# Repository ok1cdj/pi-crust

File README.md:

Pi Crust
========

This is a PCB that brings sanity to Raspberry Pi headers.

See [http://picru.st](http://picru.st) for more.

Features
--------

*   Really compact - sits *inside* the surface area of the Raspberry Pi and adds less than 2mm to the height. If you have a case for your Raspberry Pi, this board should fit inside it.
*   Pins are grouped together: GPIO, I2C, SPI, UART and power.
*   Every pin is clearly labelled added labels for RPi revision 1 and 2.
*   Connections: 2 x SPI, 2 x I2C, 1 x UART, 8 x GPIO
*   Added bidirectional 2 ports level converter
*   Uses female headers instead of male headers - you can poke jumpers right in.
*   Lots of GND and 5V pins - you need those guys a lot. These pins are duplicated where it makes sense (e.g. within the UART, I2C and SPI groups).
*   All thru-hole components - you can solder it yourself.
*   Cheapety cheapy cheap.
*   Open source hardware.
*   [More photos here](http://todayimade.co/items/joe-walnes-made-a-tiny-breakout-board-for-raspberry-pi)

See [http://picru.st](http://picru.st) for more.

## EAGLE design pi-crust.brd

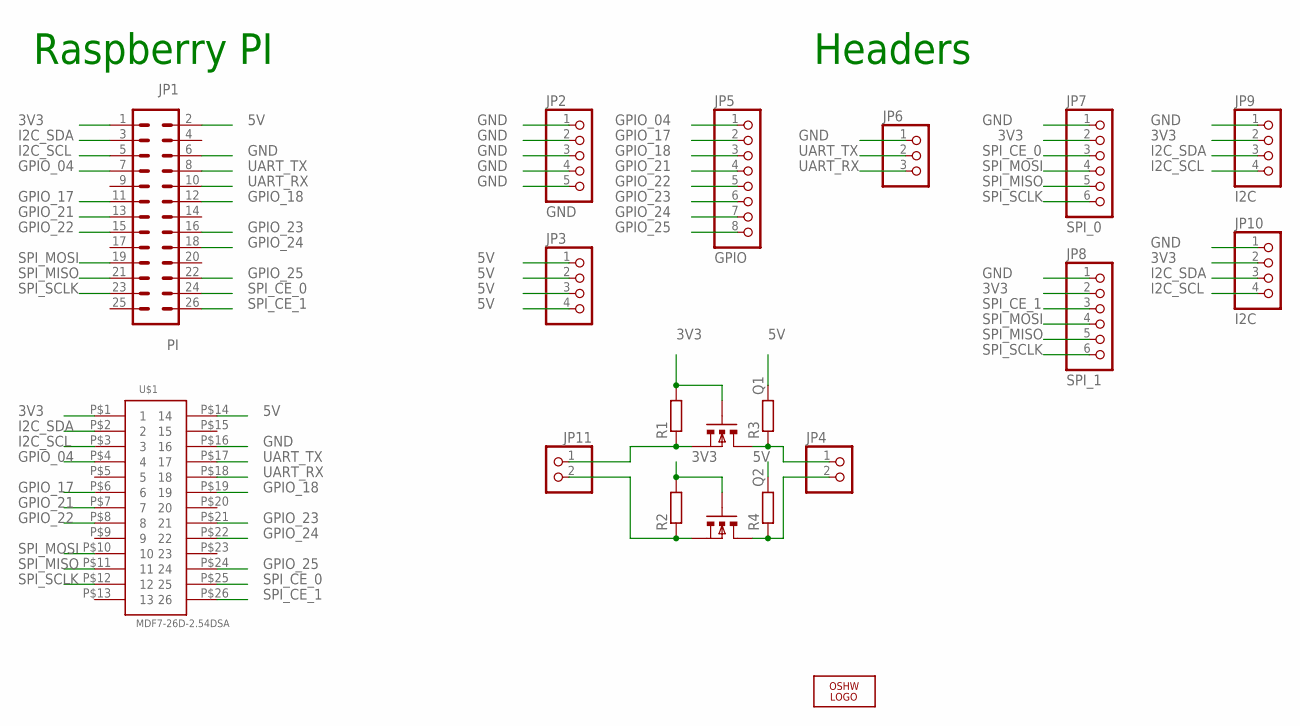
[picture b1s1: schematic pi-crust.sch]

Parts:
JP1: PI; MA13-2
JP2: GND; 1X05
JP3: PINHD-1X4; 1X04
JP4, JP11: PINHD-1X2; 1X02
JP5: GPIO; 1X08
JP6: PINHD-1X3; 1X03
JP7: SPI_0; 1X06
JP8: SPI_1; 1X06
JP9, JP10: I2C; 1X04
LOGO1: OSHW_LOGO_8MILX0100-NT; OSHW_8X100_NOTEXT
Q1, Q2: BSS138SMD; SOT23
R1, R2, R3, R4: R-EU_R0603; R0603
U$1: MDF7-26D-2.54DSA

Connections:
3V3: JP1.1, JP7.2, JP8.2, JP9.2, JP10.2, Q1.2 (G), Q2.2 (G), R1.2, R2.2, U$1.P$1 (1)
5V: JP1.2, JP3.1, JP3.2, JP3.3, JP3.4, R3.2, R4.2, U$1.P$14 (14)
GND: JP1.6, JP2.1, JP2.2, JP2.3, JP2.4, JP2.5, JP6.1, JP7.1, JP8.1, JP9.1, JP10.1, U$1.P$16 (16)
GPIO_04: JP1.7, JP5.1, U$1.P$4 (4)
GPIO_17: JP1.11, JP5.2, U$1.P$6 (6)
GPIO_18: JP1.12, JP5.3, U$1.P$19 (19)
GPIO_21: JP1.13, JP5.4, U$1.P$7 (7)
GPIO_22: JP1.15, JP5.5, U$1.P$8 (8)
GPIO_23: JP1.16, JP5.6, U$1.P$21 (21)
GPIO_24: JP1.18, JP5.7, U$1.P$22 (22)
GPIO_25: JP1.22, JP5.8, U$1.P$24 (24)
I2C_SCL: JP1.5, JP9.4, JP10.4, U$1.P$3 (3)
I2C_SDA: JP1.3, JP9.3, JP10.3, U$1.P$2 (2)
unnamed: JP11.2, Q2.1 (S), R2.1
unnamed: JP4.2, Q2.3 (D), R4.1
unnamed: JP11.1, Q1.1 (S), R1.1
unnamed: JP4.1, Q1.3 (D), R3.1
SPI_CE_0: JP1.24, JP7.3, U$1.P$25 (25)
SPI_CE_1: JP1.26, JP8.3, U$1.P$26 (26)
SPI_MISO: JP1.21, JP7.5, JP8.5, U$1.P$11 (11)
SPI_MOSI: JP1.19, JP7.4, JP8.4, U$1.P$10 (10)
SPI_SCLK: JP1.23, JP7.6, JP8.6, U$1.P$12 (12)
UART_RX: JP1.10, JP6.3, U$1.P$18 (18)
UART_TX: JP1.8, JP6.2, U$1.P$17 (17)

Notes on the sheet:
Raspberry PI
Headers

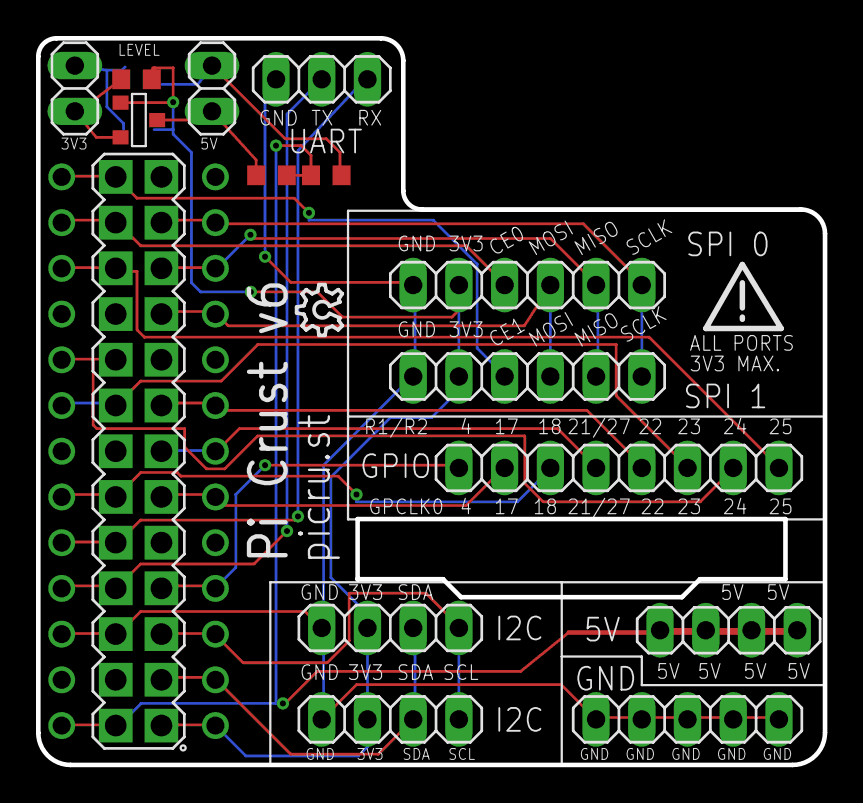
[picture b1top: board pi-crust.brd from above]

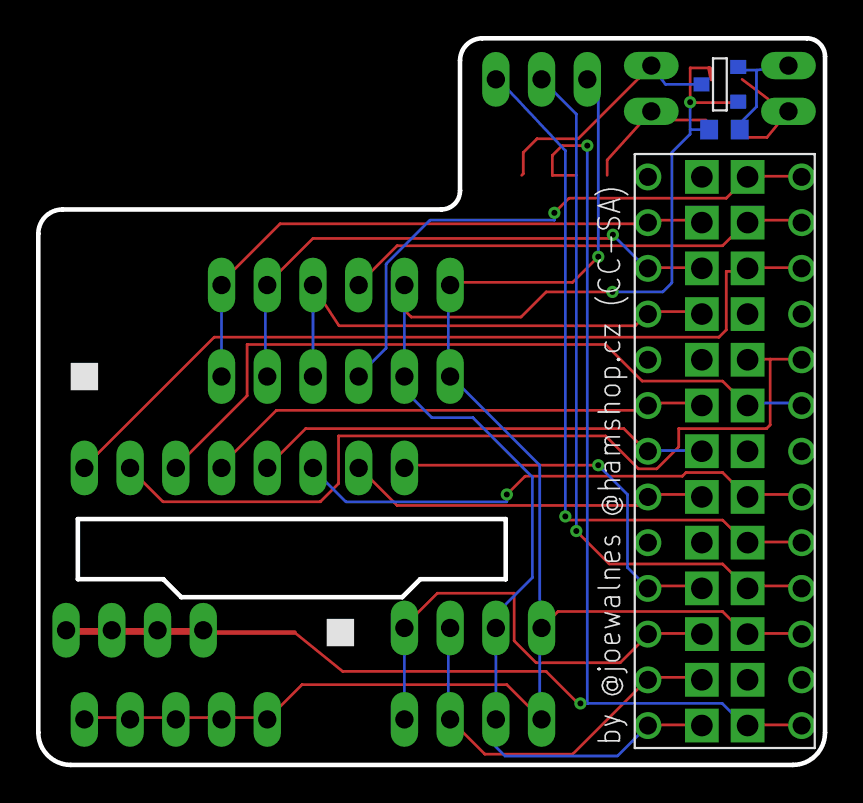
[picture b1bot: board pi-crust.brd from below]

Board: 2 copper layers, 43.7 x 40.4 mm, 19 parts (3 on the bottom side), 24 nets.

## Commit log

2014-04-13 Replaced 5V pins in ports to 3V3. Added 2 ports level converter for convert data lines from 3V3 to 5V. Updated labeling of pins for both revisions of RPi...
2014-04-14 Minor changes..
2014-04-14 Readme..
2014-04-14 New images of PCB..
2014-04-14 New images..
